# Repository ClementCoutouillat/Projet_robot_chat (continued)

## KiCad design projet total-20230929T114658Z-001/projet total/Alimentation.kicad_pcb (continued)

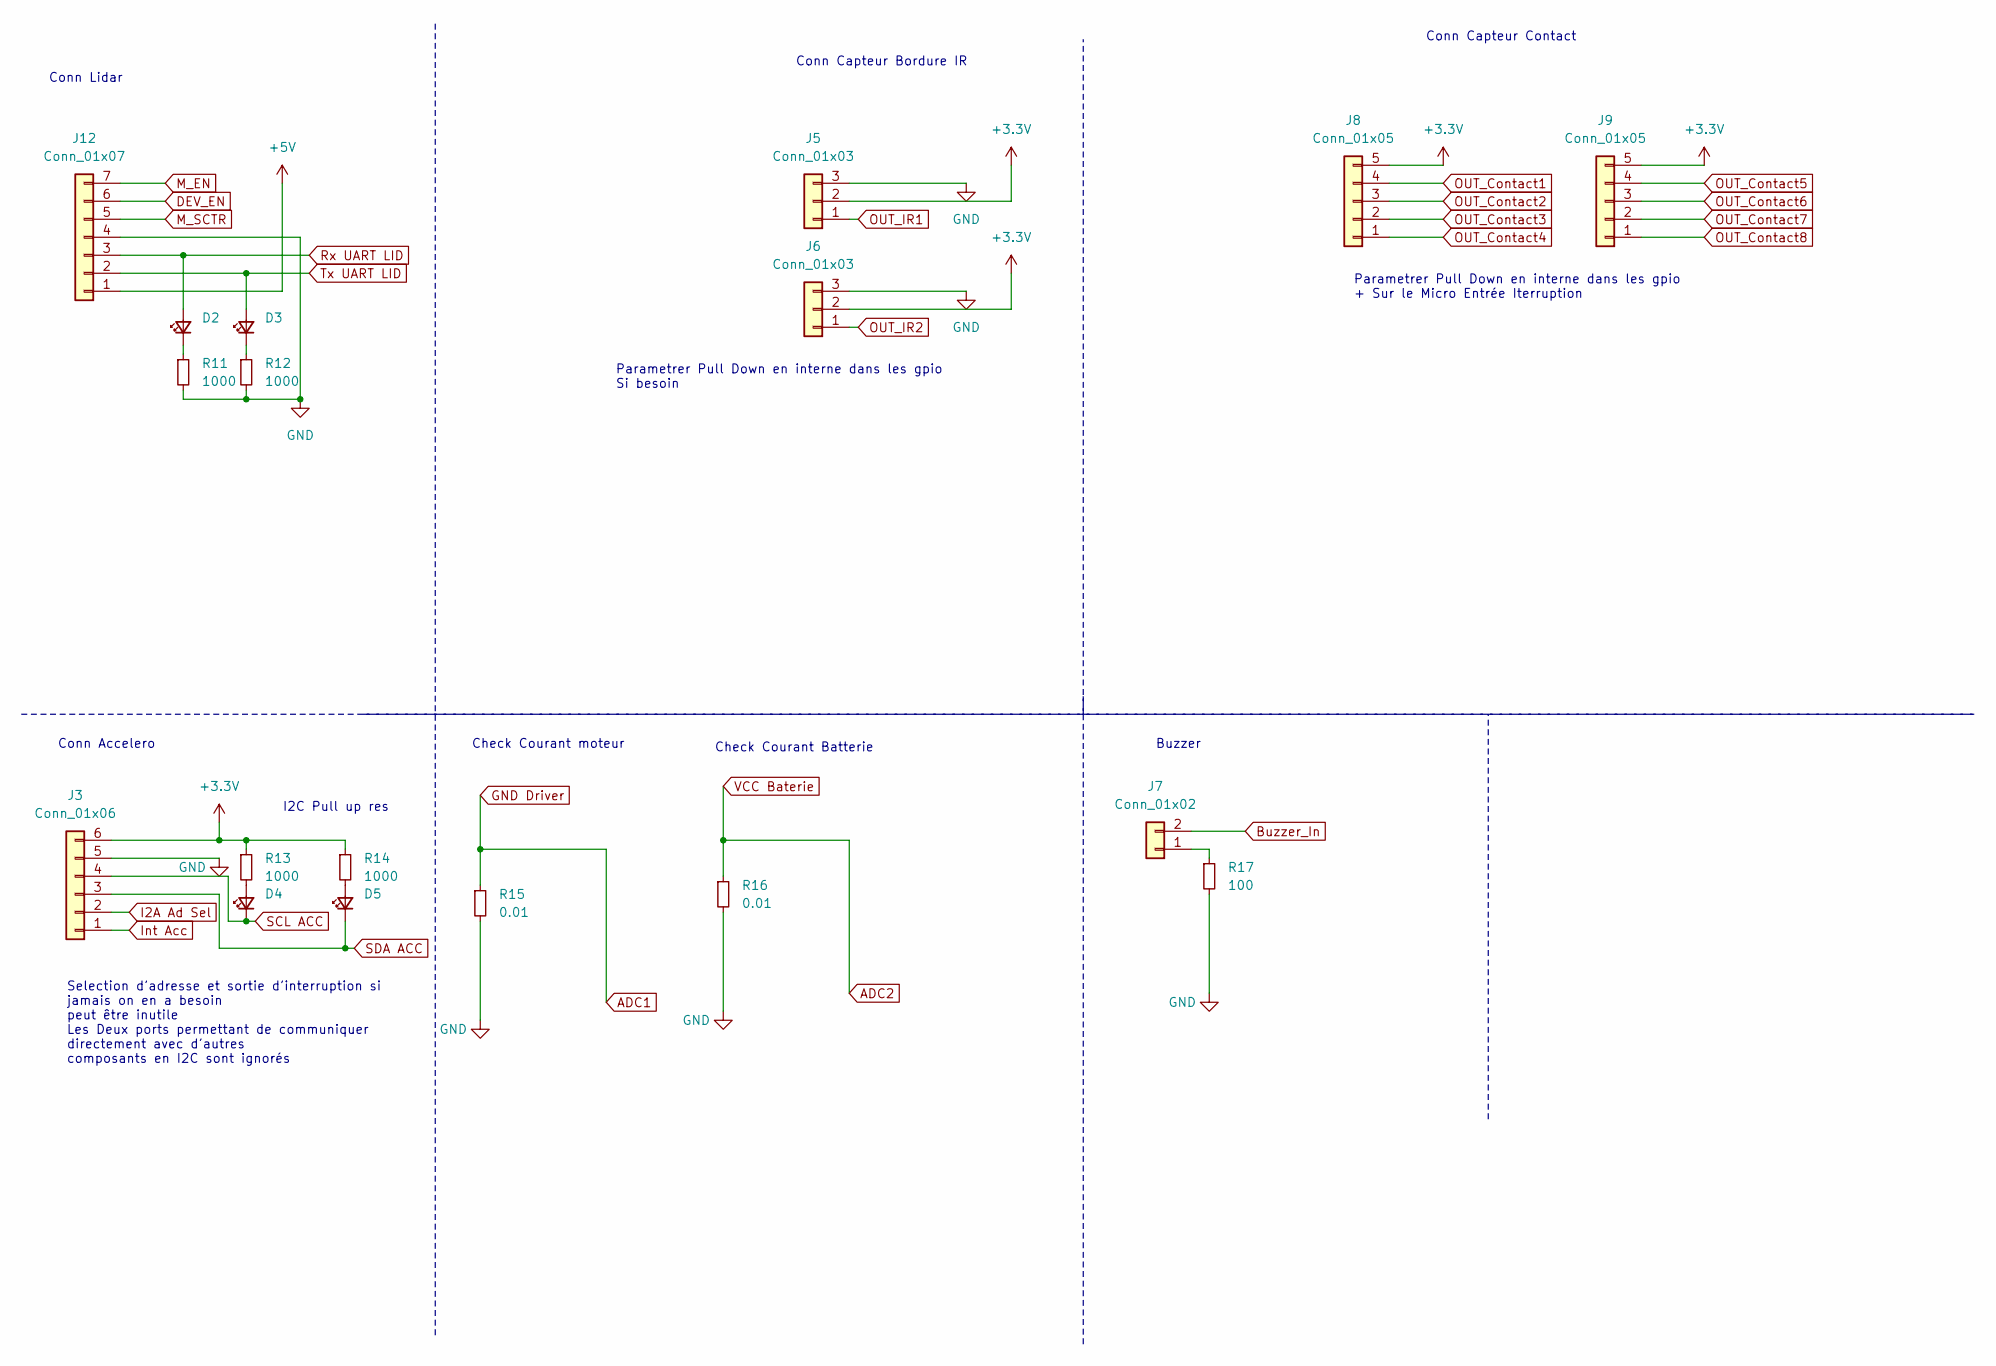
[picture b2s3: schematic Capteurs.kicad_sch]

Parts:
D2, D3, D4, D5: LED_Small; LED_0603_1608Metric_Pad1.05x0.95mm_HandSolder
J3: Conn_01x06; PinSocket_1x06_P2.54mm_Vertical
J5, J6: Conn_01x03; PinSocket_1x03_P2.54mm_Vertical
J7: Conn_01x02; PinSocket_1x02_P2.54mm_Vertical
J8, J9: Conn_01x05; PinSocket_1x05_P2.54mm_Vertical
J12: Conn_01x07; PinSocket_1x06_P2.54mm_Vertical
R11, R12, R13, R14: 1000; R_0603_1608Metric_Pad0.98x0.95mm_HandSolder
R15, R16: 0.01; R_0603_1608Metric_Pad0.98x0.95mm_HandSolder
R17: 100; R_0603_1608Metric_Pad0.98x0.95mm_HandSolder

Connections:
ADC1: R15.1; also elsewhere on the board
ADC2: R16.1; also elsewhere on the board
Buzzer_In: J7.2; also elsewhere on the board
GND: J3.5, J5.3, J6.3, J12.4, R11.2, R12.2, R15.2, R16.2, R17.2; also elsewhere on the board
I2A Ad Sel: J3.2; also elsewhere on the board
Int Acc: J3.1; also elsewhere on the board
unnamed: D2.1 (K), R11.1
unnamed: D3.1 (K), R12.1
unnamed: D4.2 (A), R13.2
unnamed: D5.2 (A), R14.2
unnamed: J7.1, R17.1
OUT_Contact1: J8.4; also elsewhere on the board
OUT_Contact2: J8.3; also elsewhere on the board
OUT_Contact3: J8.2; also elsewhere on the board
OUT_Contact4: J8.1; also elsewhere on the board
OUT_Contact5: J9.4; also elsewhere on the board
OUT_Contact6: J9.3; also elsewhere on the board
OUT_Contact7: J9.2; also elsewhere on the board
OUT_Contact8: J9.1; also elsewhere on the board
OUT_IR1: J5.1; also elsewhere on the board
OUT_IR2: J6.1; also elsewhere on the board
Rx UART LID: D2.2 (A), J12.3; also elsewhere on the board
SCL ACC: D4.1 (K), J3.4; also elsewhere on the board
SDA ACC: D5.1 (K), J3.3; also elsewhere on the board
Tx UART LID: D3.2 (A), J12.2; also elsewhere on the board

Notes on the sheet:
Check Courant moteur
Buzzer
Parametrer Pull Down en interne dans les gpio + Sur le Micro Entrée Iterruption
Check Courant Batterie
Conn Lidar
Conn Accelero
Conn Capteur Contact
Parametrer Pull Down en interne dans les gpio Si besoin
I2C Pull up res
Selection d'adresse et sortie d'interruption si jamais on en a besoin peut être inutile Les Deux ports permettant de communiquer directement avec d'autres composants en I2C sont ignorés
Conn Capteur Bordure IR

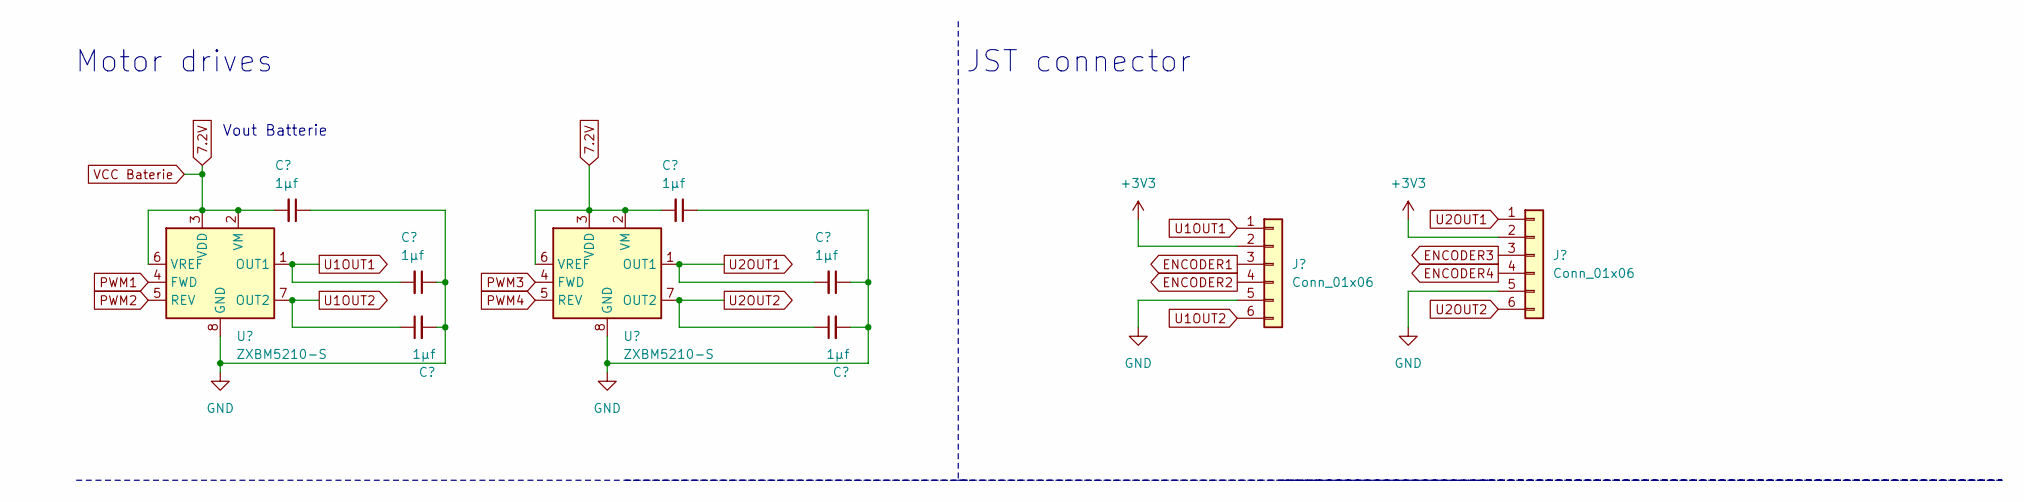
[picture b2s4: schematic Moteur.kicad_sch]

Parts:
C20, C21, C22, C23, C24, C25: 1µf; C_0603_1608Metric_Pad1.08x0.95mm_HandSolder
J10, J11: Conn_01x06; PinSocket_1x06_P2.54mm_Vertical
U3, U4: ZXBM5210-S; SOIC-8_3.9x4.9mm_P1.27mm

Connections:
7.2V: C20.2, C23.2, U3.2 (VM), U3.3 (VDD), U3.6 (VREF), U4.2 (VM), U4.3 (VDD), U4.6 (VREF); also elsewhere on the board
ENCODER1: J10.3; also elsewhere on the board
ENCODER2: J10.4; also elsewhere on the board
ENCODER3: J11.3; also elsewhere on the board
ENCODER4: J11.4; also elsewhere on the board
GND: C20.1, C21.1, C22.2, C23.1, C24.1, C25.2, J10.5, J11.5, U3.8 (GND), U4.8 (GND); also elsewhere on the board
PWM1: U3.4 (FWD); also elsewhere on the board
PWM2: U3.5 (REV); also elsewhere on the board
PWM3: U4.4 (FWD); also elsewhere on the board
PWM4: U4.5 (REV); also elsewhere on the board
U1OUT1: C21.2, J10.1, U3.1 (OUT1)
U1OUT2: C22.1, J10.6, U3.7 (OUT2)
U2OUT1: C24.2, J11.1, U4.1 (OUT1)
U2OUT2: C25.1, J11.6, U4.7 (OUT2)

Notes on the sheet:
JST connector
Vout Batterie
Motor drives

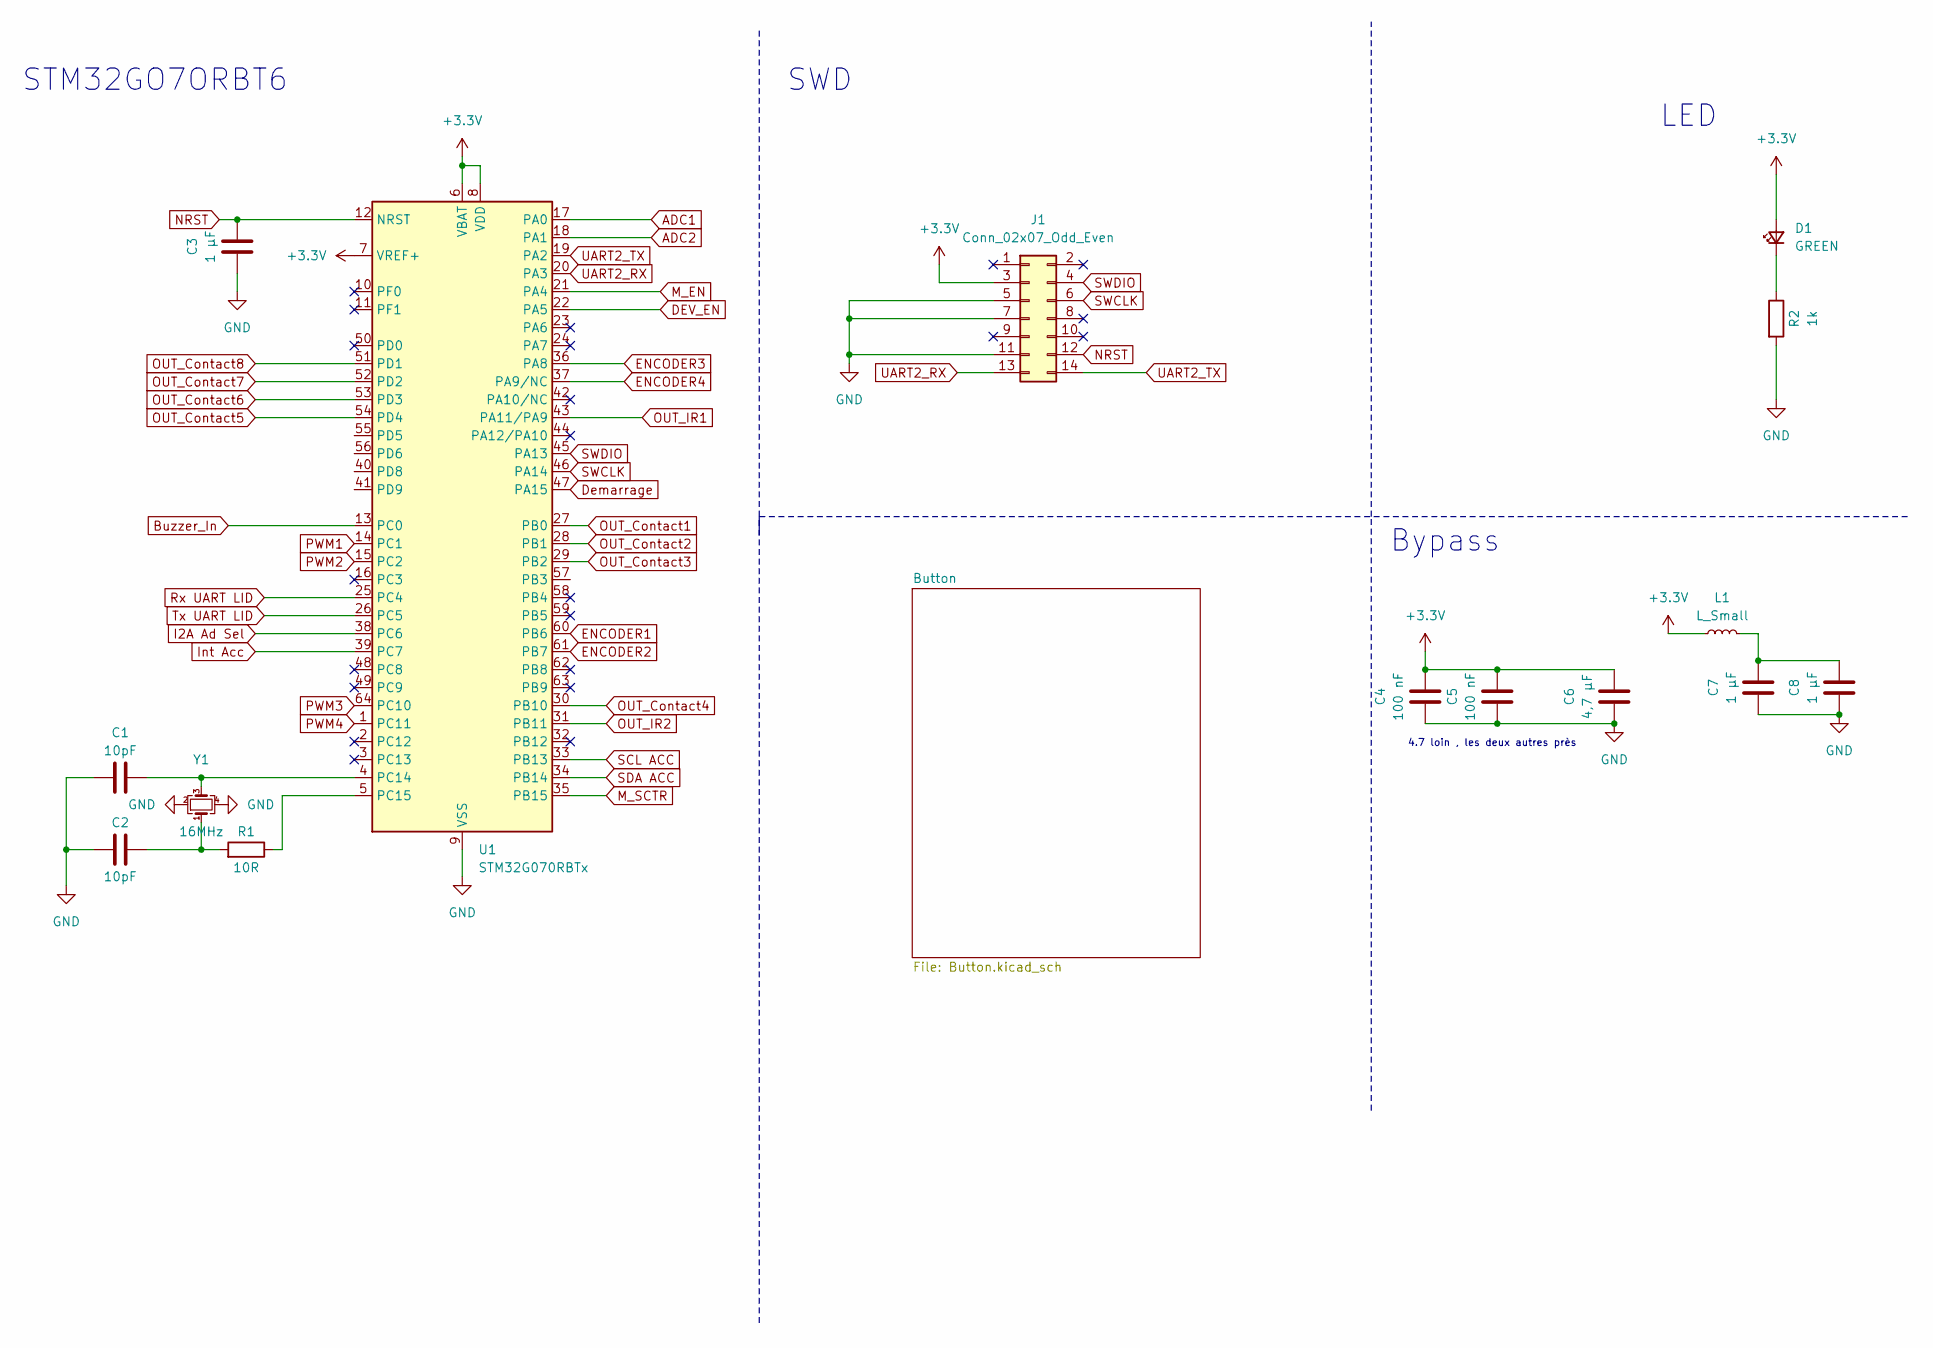
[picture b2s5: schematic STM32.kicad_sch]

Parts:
C1, C2: 10pF; C_0603_1608Metric_Pad1.08x0.95mm_HandSolder
C3, C7, C8: 1 µF; C_0603_1608Metric_Pad1.08x0.95mm_HandSolder
C4, C5: 100 nF; C_0603_1608Metric_Pad1.08x0.95mm_HandSolder
C6: 4,7 µF; C_0603_1608Metric_Pad1.08x0.95mm_HandSolder
D1: GREEN; LED_0603_1608Metric_Pad1.05x0.95mm_HandSolder
J1: Conn_02x07_Odd_Even; PinHeader_2x07_P1.27mm_Vertical_SMD
L1: L_Small; L_0603_1608Metric_Pad1.05x0.95mm_HandSolder
R1: 10R; R_0603_1608Metric_Pad0.98x0.95mm_HandSolder
R2: 1k; R_0603_1608Metric_Pad0.98x0.95mm_HandSolder
U1: STM32G070RBTx; LQFP-64_10x10mm_P0.5mm
Y1: 16MHz; Crystal_SMD_EuroQuartz_MT-4Pin_3.2x2.5mm

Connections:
ADC1: U1.17 (PA0); also elsewhere on the board
ADC2: U1.18 (PA1); also elsewhere on the board
Buzzer_In: U1.13 (PC0); also elsewhere on the board
DEV_EN: U1.22 (PA5); also elsewhere on the board
Demarrage: U1.47 (PA15); also elsewhere on the board
ENCODER1: U1.60 (PB6); also elsewhere on the board
ENCODER2: U1.61 (PB7); also elsewhere on the board
ENCODER3: U1.36 (PA8); also elsewhere on the board
ENCODER4: U1.37 (PA9/NC); also elsewhere on the board
GND: C1.1, C2.1, C3.1, C4.1, C5.1, C6.1, C7.1, C8.1, J1.5, J1.7, J1.11, R2.2, U1.9 (VSS), Y1.2, Y1.4; also elsewhere on the board
I2A Ad Sel: U1.38 (PC6); also elsewhere on the board
Int Acc: U1.39 (PC7); also elsewhere on the board
M_EN: U1.21 (PA4); also elsewhere on the board
M_SCTR: U1.35 (PB15); also elsewhere on the board
NRST: C3.2, J1.12, U1.12 (NRST); also elsewhere on the board
unnamed: C2.2, R1.2, Y1.1
unnamed: C7.2, C8.2, L1.2
unnamed: D1.1 (K), R2.1
unnamed: C1.2, U1.4 (PC14), Y1.3
unnamed: R1.1, U1.5 (PC15)
OUT_Contact1: U1.27 (PB0); also elsewhere on the board
OUT_Contact2: U1.28 (PB1); also elsewhere on the board
OUT_Contact3: U1.29 (PB2); also elsewhere on the board
OUT_Contact4: U1.30 (PB10); also elsewhere on the board
OUT_Contact5: U1.54 (PD4); also elsewhere on the board
OUT_Contact6: U1.53 (PD3); also elsewhere on the board
OUT_Contact7: U1.52 (PD2); also elsewhere on the board
OUT_Contact8: U1.51 (PD1); also elsewhere on the board
OUT_IR1: U1.43 (PA11/PA9); also elsewhere on the board
OUT_IR2: U1.44 (PA12/PA10); also elsewhere on the board
PWM1: U1.14 (PC1); also elsewhere on the board
PWM2: U1.15 (PC2); also elsewhere on the board
PWM3: U1.64 (PC10); also elsewhere on the board
PWM4: U1.1 (PC11); also elsewhere on the board
Rx UART LID: U1.25 (PC4); also elsewhere on the board
SCL ACC: U1.33 (PB13); also elsewhere on the board
SDA ACC: U1.34 (PB14); also elsewhere on the board
SWCLK: J1.6, U1.46 (PA14)
SWDIO: J1.4, U1.45 (PA13)
Tx UART LID: U1.26 (PC5); also elsewhere on the board
UART2_RX: J1.13, U1.20 (PA3)
UART2_TX: J1.14, U1.19 (PA2)

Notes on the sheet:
STM32GO7ORBT6
Bypass
LED
SWD
4.7 loin , les deux autres près

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
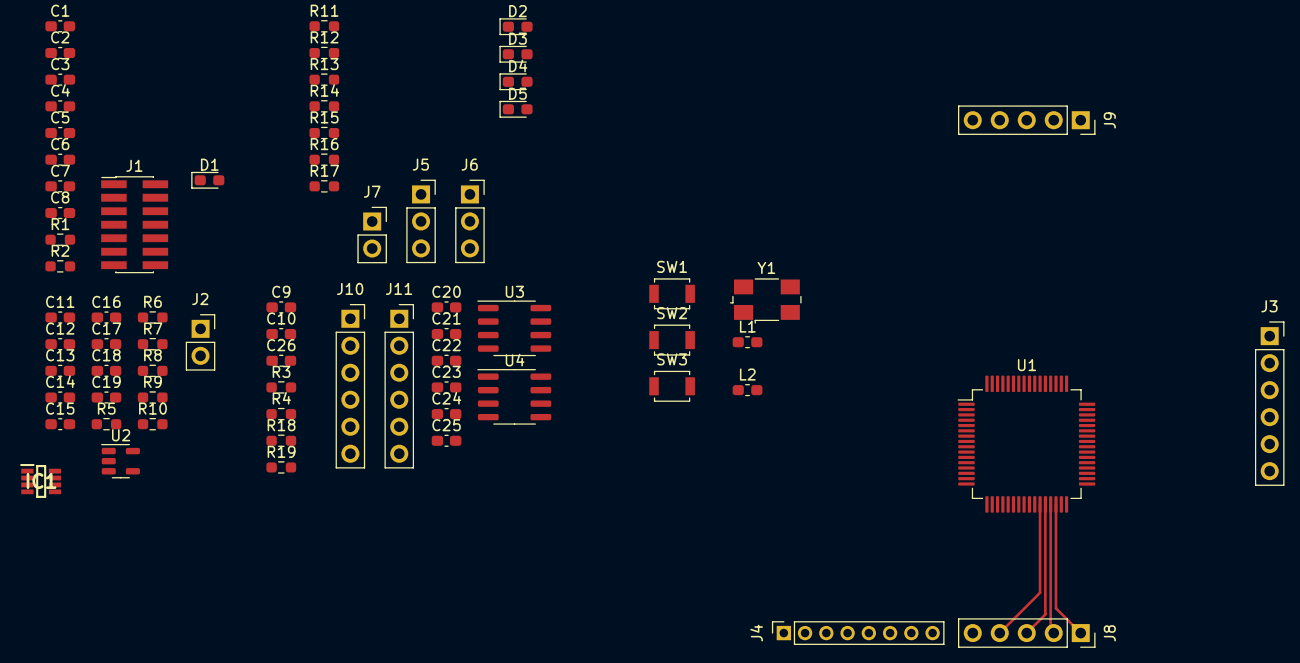
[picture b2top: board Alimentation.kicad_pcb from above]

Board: 2 copper layers, 72 parts (0 on the bottom side), 66 nets.

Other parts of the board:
J4: Conn_01x08; PinSocket_1x08_P2.00mm_Vertical

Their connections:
+5V: J4.1; also elsewhere on the board
DEV_EN: J4.6; also elsewhere on the board
GND: J4.4; also elsewhere on the board
M_EN: J4.7; also elsewhere on the board
M_SCTR: J4.5; also elsewhere on the board
Rx UART LID: J4.3; also elsewhere on the board
Tx UART LID: J4.2; also elsewhere on the board

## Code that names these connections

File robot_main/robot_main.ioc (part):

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Mcu.Name=STM32G070RBTx
Mcu.Package=LQFP64
Mcu.UserName=STM32G070RBTx
PA0.GPIOParameters=GPIO_Label
PA0.GPIO_Label=LIDAR_TX
PA0.Mode=Asynchronous
PA0.Signal=USART4_TX
PA1.GPIOParameters=GPIO_Label
PA1.GPIO_Label=LIDAR_RX
PA1.Mode=Asynchronous
PA1.Signal=USART4_RX
PA13.Mode=Serial_Wire
PA13.Signal=SYS_SWDIO
PA14-BOOT0.Mode=Serial_Wire
PA14-BOOT0.Signal=SYS_SWCLK
PA8.Signal=S_TIM1_CH1
PA9.Signal=S_TIM1_CH2
PB11.GPIOParameters=GPIO_Label
PB11.GPIO_Label=LED_RED
PB11.Signal=GPIO_Output
PB12.GPIOParameters=GPIO_Label
PB12.GPIO_Label=LED_ORANGE
PB12.Signal=GPIO_Output
PB13.GPIOParameters=GPIO_Label
PB13.GPIO_Label=LED_GREEN
PB13.Signal=GPIO_Output
PB14.Signal=S_TIM15_CH1
PB15.Signal=S_TIM15_CH2
PB6.GPIOParameters=GPIO_PuPd,GPIO_Label
PB6.GPIO_Label=BUMPER4
PB6.GPIO_PuPd=GPIO_PULLUP
PB6.Signal=GPXTI6
PB7.GPIOParameters=GPIO_PuPd,GPIO_Label
PB7.GPIO_Label=BUMPER3
PB7.GPIO_PuPd=GPIO_PULLUP
PB7.Signal=GPXTI7
PB8.GPIOParameters=GPIO_PuPd,GPIO_Label
PB8.GPIO_Label=BUMPER2
PB8.GPIO_PuPd=GPIO_PULLUP
PB8.Signal=GPXTI8
PB9.GPIOParameters=GPIO_PuPd,GPIO_Label
PB9.GPIO_Label=BUMPER1
PB9.GPIO_PuPd=GPIO_PULLUP
PB9.Signal=GPXTI9
PC14-OSC32_IN\ (PC14).Mode=LSE-External-Oscillator
PC14-OSC32_IN\ (PC14).Signal=RCC_OSC32_IN
PC15-OSC32_OUT\ (PC15).Mode=LSE-External-Oscillator
PC15-OSC32_OUT\ (PC15).Signal=RCC_OSC32_OUT
PC6.Signal=S_TIM3_CH1
PC7.Signal=S_TIM3_CH2
PD0.Signal=S_TIM16_CH1
PD1.Signal=S_TIM17_CH1
PD2.GPIOParameters=GPIO_Label
PD2.GPIO_Label=BORDER_BACK
PD2.Signal=GPXTI2
PD3.GPIOParameters=GPIO_Label
PD3.GPIO_Label=BORDER_FRONT
PD3.Signal=GPXTI3
PD5.Mode=Asynchronous
PD5.Signal=USART2_TX
PD6.Mode=Asynchronous
PD6.Signal=USART2_RX
PF0-OSC_IN\ (PF0).Mode=HSE-External-Oscillator
PF0-OSC_IN\ (PF0).Signal=RCC_OSC_IN
PF1-OSC_OUT\ (PF1).Mode=HSE-External-Oscillator
PF1-OSC_OUT\ (PF1).Signal=RCC_OSC_OUT
RCC.HSE_VALUE=16000000
RCC.SYSCLKFreq_VALUE=64000000
RCC.SYSCLKSource=RCC_SYSCLKSOURCE_PLLCLK
board=custom

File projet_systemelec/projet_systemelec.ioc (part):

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Mcu.Name=STM32G070RBTx
Mcu.Package=LQFP64
Mcu.UserName=STM32G070RBTx
PA2.Mode=Asynchronous
PA2.Signal=USART2_TX
PA3.Mode=Asynchronous
PA3.Signal=USART2_RX
PA8.Signal=S_TIM1_CH1
PA9.Signal=S_TIM1_CH2
PB15.Signal=S_TIM15_CH2
PB4.Signal=S_TIM3_CH1
PB5.Signal=S_TIM3_CH2
PB8.Signal=S_TIM16_CH1
PB9.Signal=S_TIM17_CH1
PC12.Signal=S_TIM14_CH1
PC14-OSC32_IN\ (PC14).Mode=LSE-External-Oscillator
PC14-OSC32_IN\ (PC14).Signal=RCC_OSC32_IN
PC15-OSC32_OUT\ (PC15).Mode=LSE-External-Oscillator
PC15-OSC32_OUT\ (PC15).Signal=RCC_OSC32_OUT
PF0-OSC_IN\ (PF0).Mode=HSE-External-Oscillator
PF0-OSC_IN\ (PF0).Signal=RCC_OSC_IN
PF1-OSC_OUT\ (PF1).Mode=HSE-External-Oscillator
PF1-OSC_OUT\ (PF1).Signal=RCC_OSC_OUT
RCC.HSE_VALUE=8000000
RCC.SYSCLKFreq_VALUE=16000000
board=custom

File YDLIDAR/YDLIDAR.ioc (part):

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Mcu.Name=STM32F410R(8-B)Tx
Mcu.Package=LQFP64
Mcu.UserName=STM32F410RBTx
PA10.Mode=Asynchronous
PA10.Signal=USART1_RX
PA13.GPIOParameters=GPIO_Label
PA13.GPIO_Label=TMS
PA13.Mode=Serial_Wire
PA13.Signal=SYS_JTMS-SWDIO
PA14.GPIOParameters=GPIO_Label
PA14.GPIO_Label=TCK
PA14.Mode=Serial_Wire
PA14.Signal=SYS_JTCK-SWCLK
PA2.GPIOParameters=GPIO_Label
PA2.GPIO_Label=USART_TX
PA2.Mode=Asynchronous
PA2.Signal=USART2_TX
PA3.GPIOParameters=GPIO_Label
PA3.GPIO_Label=USART_RX
PA3.Mode=Asynchronous
PA3.Signal=USART2_RX
PA5.GPIOParameters=GPIO_Label
PA5.GPIO_Label=LD2 [Green Led]
PA5.Signal=GPIO_Output
PA9.Mode=Asynchronous
PA9.Signal=USART1_TX
PB3.GPIOParameters=GPIO_Label
PB3.GPIO_Label=SWO
PB3.Signal=SYS_JTDO-SWO
PC13-ANTI_TAMP.GPIOParameters=GPIO_Label,GPIO_ModeDefaultEXTI
PC13-ANTI_TAMP.GPIO_Label=B1 [Blue PushButton]
PC13-ANTI_TAMP.GPIO_ModeDefaultEXTI=GPIO_MODE_IT_FALLING
PC13-ANTI_TAMP.Signal=GPXTI13
PC14-OSC32_IN.Mode=LSE-External-Oscillator
PC14-OSC32_IN.Signal=RCC_OSC32_IN
PC15-OSC32_OUT.Mode=LSE-External-Oscillator
PC15-OSC32_OUT.Signal=RCC_OSC32_OUT
PH0\ -\ OSC_IN.Mode=HSE-External-Clock-Source
PH0\ -\ OSC_IN.Signal=RCC_OSC_IN
PH1\ -\ OSC_OUT.Mode=HSE-External-Clock-Source
PH1\ -\ OSC_OUT.Signal=RCC_OSC_OUT
RCC.HSE_VALUE=8000000
RCC.SYSCLKFreq_VALUE=84000000
RCC.SYSCLKSource=RCC_SYSCLKSOURCE_PLLCLK
board=NUCLEO-F410RB
boardIOC=true

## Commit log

2023-10-12 nouvelle version
2023-10-19 main
2023-10-19 Carte a router
2023-10-26 README.md
2023-10-26 1er version code modeur, faut test en vrai pour regle les parametre PID
2023-10-29 can read data from lidar ,but need to update
2023-10-29 add comment to Ydliaer.c
2023-11-29 REMOVE YDLIDER
2023-11-29 RECONFIG FINISHED
2023-11-29 config uart boterate 128000
2023-11-29 run right
2023-11-29 add doc
2023-11-30 code can get angle and distance
2023-11-30 add test
2023-11-30 ignore metadata
2023-12-14 test receive buffer
2023-12-15 save the dataprocess version 1 and version2
2023-12-15 data process wroks and finished
2023-12-16 restartScan FUNCIOTN
2023-12-16 ydlider is finished
2023-12-18 add some file
2023-12-19 test
2023-12-19 just software
2023-12-19 rename the pins
2023-12-19 remove ydliar
2023-12-19 now free rtos founction well
2023-12-19 create tesk successfully
2023-12-19 sumit gitignore
2023-12-19 add ydlidar driver
2023-12-19 debug the warning
2023-12-19 updata uart DMA
2023-12-19 update uart dma
2023-12-19 Update stm32g0xx_it.c by Bastien
2023-12-19 tead
2023-12-19 add changes
2023-12-19 modeur version2
2023-12-20 update the code interface
2023-12-20 version3
2023-12-20 test the task
2023-12-20 update the motorinterface
2023-12-20 add motor
2023-12-20 version4
2023-12-20 motor founction well
2023-12-21 motor foucntion well
2023-12-21 New stm32g0xx_it.c : Bumper interrupt by Bastien
2023-12-21 ydlidar founction well
2023-12-21 uodate the interrupt
2023-12-27 founction well
2023-12-28 finished add the chat and the souris task
2023-12-28 obstacleAngleAndDistances founction finished
2023-12-30 add chat tesk and souris task
2023-12-31 finished the code
2024-01-08 ydlider founction
2024-01-09 add ydlidar protocol files finished
2024-01-10 freertos works
2024-01-11 add queue to the ydlidar
2024-01-12 souris mode fonction
2024-01-12 we finished the project
2024-01-14 remove test
2024-01-15 readme title
